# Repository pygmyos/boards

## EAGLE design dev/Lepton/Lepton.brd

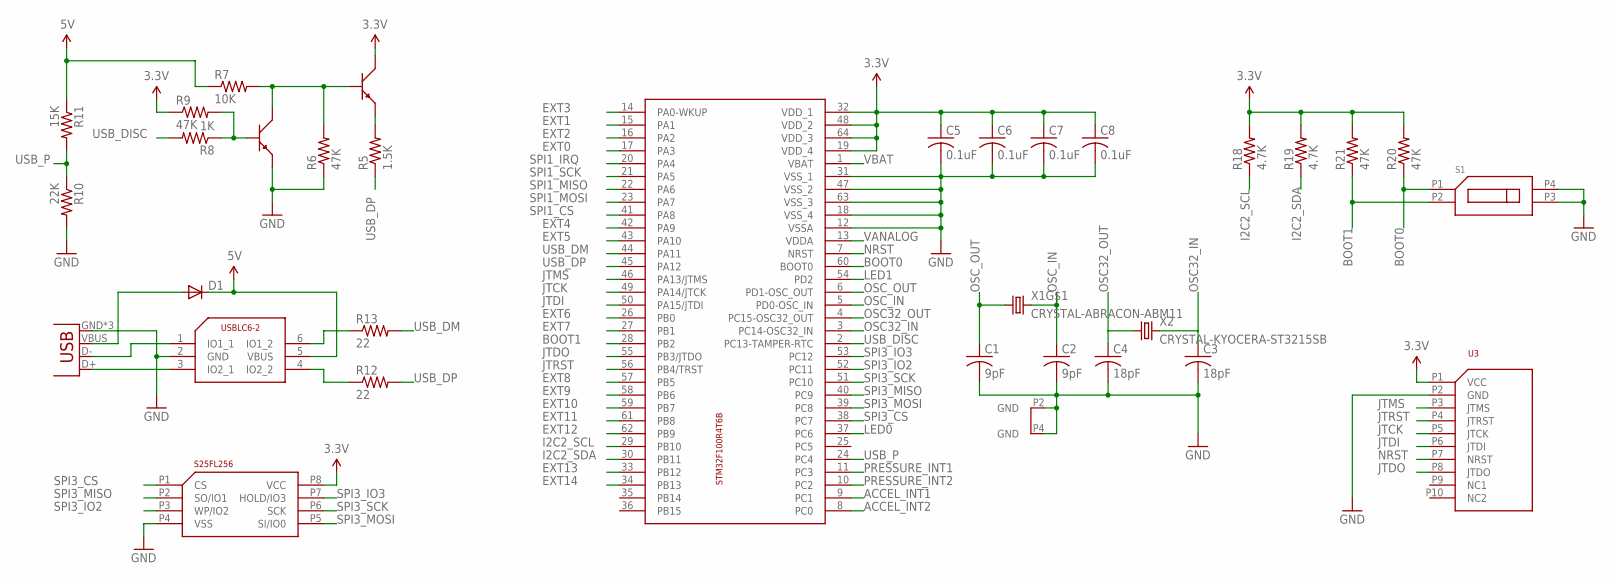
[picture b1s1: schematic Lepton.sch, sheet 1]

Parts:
C1, C2: 9pF; C0201
C3, C4: 18pF; C0201
C5, C6, C7, C8: 0.1uF; C0201
D1: DIODE-MINIMELF; MINIMELF
JP1: USB-MICROB
R5: 1.5K; R0402
R6: 47K; R0402
R7: 10K; R0201
R8: 1K; R0201
R9, R20, R21: 47K; R0201
R10: 22K; R0201
R11: 15K; R0201
R12, R13: 22; R0201
R18, R19: 4.7K; R0201
S1: SWITCH-DIP-GDH-02
U2: STM32F100R4T6B; S-PQFP64-G64
U3: STM32-JTAG-FFC; FCI-FFC-10P-51281-1494
U$1: SPANSION-S25FL256; SPANSION-WSON-8
U$2, U$3: BIPOLAR-PMBT6428; DUBLIB_SOT23
U$4: USBLC6-2; SOT23-6L
X1: CRYSTAL-ABRACON-ABM11; ABM11
X2: CRYSTAL-KYOCERA-ST3215SB

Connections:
3.3V: C5.1, C6.1, C7.1, C8.1, R9.1, R18.2, R19.2, R20.2, R21.2, U2.19 (VDD_4), U2.32 (VDD_1), U2.48 (VDD_2), U2.64 (VDD_3), U3.P1 (VCC), U$1.P8 (VCC), U$2.3; also elsewhere on the board
5V: D1.C, R7.1, R11.1, U$4.5 (VBUS); also elsewhere on the board
ACCEL_INT1: U2.9 (PC1)
ACCEL_INT2: U2.8 (PC0); also elsewhere on the board
BOOT0: R20.1, S1.P1 (SW0_0), U2.60 (BOOT0)
BOOT1: R21.1, S1.P2 (SW1_0), U2.28 (PB2)
EXT0: U2.17 (PA3); also elsewhere on the board
EXT1: U2.15 (PA1); also elsewhere on the board
EXT2: U2.16 (PA2); also elsewhere on the board
EXT3: U2.14 (PA0-WKUP); also elsewhere on the board
EXT4: U2.42 (PA9); also elsewhere on the board
EXT5: U2.43 (PA10); also elsewhere on the board
EXT6: U2.26 (PB0); also elsewhere on the board
EXT7: U2.27 (PB1); also elsewhere on the board
EXT8: U2.57 (PB5); also elsewhere on the board
EXT9: U2.58 (PB6); also elsewhere on the board
EXT10: U2.59 (PB7); also elsewhere on the board
EXT11: U2.61 (PB8); also elsewhere on the board
EXT12: U2.62 (PB9); also elsewhere on the board
EXT13: U2.33 (PB12); also elsewhere on the board
EXT14: U2.34 (PB13); also elsewhere on the board
GND: C1.2, C2.2, C3.2, C4.2, C5.2, C6.2, C7.2, C8.2, JP1.GND, JP1.MT1 (GND), JP1.MT2 (GND), R6.1, R10.2, S1.P3 (SW1_1), S1.P4 (SW0_1), U2.12 (VSSA), U2.18 (VSS_4), U2.31 (VSS_1), U2.47 (VSS_2), U2.63 (VSS_3), U3.P2 (GND), U$1.P4 (VSS), U$3.2, U$4.2 (GND), X1.P2 (GND), X1.P4 (GND); also elsewhere on the board
I2C2_SCL: R18.1, U2.29 (PB10); also elsewhere on the board
I2C2_SDA: R19.1, U2.30 (PB11); also elsewhere on the board
JTCK: U2.49 (PA14/JTCK), U3.P5 (JTCK)
JTDI: U2.50 (PA15/JTDI), U3.P6 (JTDI)
JTDO: U2.55 (PB3/JTDO), U3.P8 (JTDO)
JTMS: U2.46 (PA13/JTMS), U3.P3 (JTMS)
JTRST: U2.56 (PB4/TRST), U3.P4 (JTRST)
LED0: U2.37 (PC6); also elsewhere on the board
LED1: U2.54 (PD2); also elsewhere on the board
unnamed: JP1.D+, U$4.3 (IO2_1)
unnamed: JP1.D-, U$4.1 (IO1_1)
unnamed: D1.A, JP1.VBUS
unnamed: R13.1, U$4.6 (IO1_2)
unnamed: R5.2, U$2.2
unnamed: R6.2, R7.2, U$2.1, U$3.3
unnamed: R8.1, R9.2, U$3.1
unnamed: R12.1, U$4.4 (IO2_2)
NRST: U2.7 (NRST), U3.P7 (NRST)
OSC32_IN: C3.1, U2.3 (PC14-OSC32_IN), X2.P2 (2)
OSC32_OUT: C4.1, U2.4 (PC15-OSC32_OUT), X2.P1 (1)
OSC_IN: C2.1, U2.5 (PD0-OSC_IN), X1.P3 (2)
OSC_OUT: C1.1, U2.6 (PD1-OSC_OUT), X1.P1 (1)
PRESSURE_INT1: U2.11 (PC3); also elsewhere on the board
PRESSURE_INT2: U2.10 (PC2); also elsewhere on the board
SPI1_CS: U2.41 (PA8); also elsewhere on the board
SPI1_IRQ: U2.20 (PA4); also elsewhere on the board
SPI1_MISO: U2.22 (PA6); also elsewhere on the board
SPI1_MOSI: U2.23 (PA7); also elsewhere on the board
SPI1_SCK: U2.21 (PA5); also elsewhere on the board
SPI3_CS: U2.38 (PC7), U$1.P1 (CS)
SPI3_IO2: U2.52 (PC11), U$1.P3 (WP/IO2)
SPI3_IO3: U2.53 (PC12), U$1.P7 (HOLD/IO3)
SPI3_MISO: U2.40 (PC9), U$1.P2 (SO/IO1)
SPI3_MOSI: U2.39 (PC8), U$1.P5 (SI/IO0)
SPI3_SCK: U2.51 (PC10), U$1.P6 (SCK)
USB_DISC: R8.2, U2.2 (PC13-TAMPER-RTC); also elsewhere on the board
USB_DM: R13.2, U2.44 (PA11); also elsewhere on the board
USB_DP: R5.1, R12.2, U2.45 (PA12); also elsewhere on the board
USB_P: R10.1, R11.2, U2.24 (PC4)
VANALOG: U2.13 (VDDA); also elsewhere on the board
VBAT: U2.1 (VBAT); also elsewhere on the board

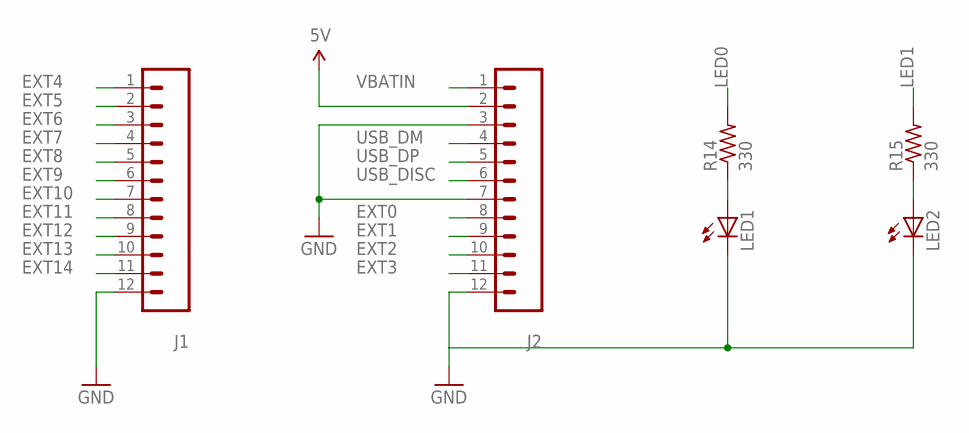
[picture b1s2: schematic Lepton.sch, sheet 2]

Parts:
J1, J2: M12; 1X12
LED1, LED2: LED0603; LED-0603
R14, R15: 330; R0201

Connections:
5V: J2.2; also elsewhere on the board
EXT0: J2.8; also elsewhere on the board
EXT1: J2.9; also elsewhere on the board
EXT2: J2.10; also elsewhere on the board
EXT3: J2.11; also elsewhere on the board
EXT4: J1.1; also elsewhere on the board
EXT5: J1.2; also elsewhere on the board
EXT6: J1.3; also elsewhere on the board
EXT7: J1.4; also elsewhere on the board
EXT8: J1.5; also elsewhere on the board
EXT9: J1.6; also elsewhere on the board
EXT10: J1.7; also elsewhere on the board
EXT11: J1.8; also elsewhere on the board
EXT12: J1.9; also elsewhere on the board
EXT13: J1.10; also elsewhere on the board
EXT14: J1.11; also elsewhere on the board
GND: J1.12, J2.3, J2.7, J2.12, LED1.C, LED2.C; also elsewhere on the board
LED0: R14.2; also elsewhere on the board
LED1: R15.2; also elsewhere on the board
unnamed: LED1.A, R14.1
unnamed: LED2.A, R15.1
USB_DISC: J2.6; also elsewhere on the board
USB_DM: J2.4; also elsewhere on the board
USB_DP: J2.5; also elsewhere on the board
VBATIN: J2.1; also elsewhere on the board

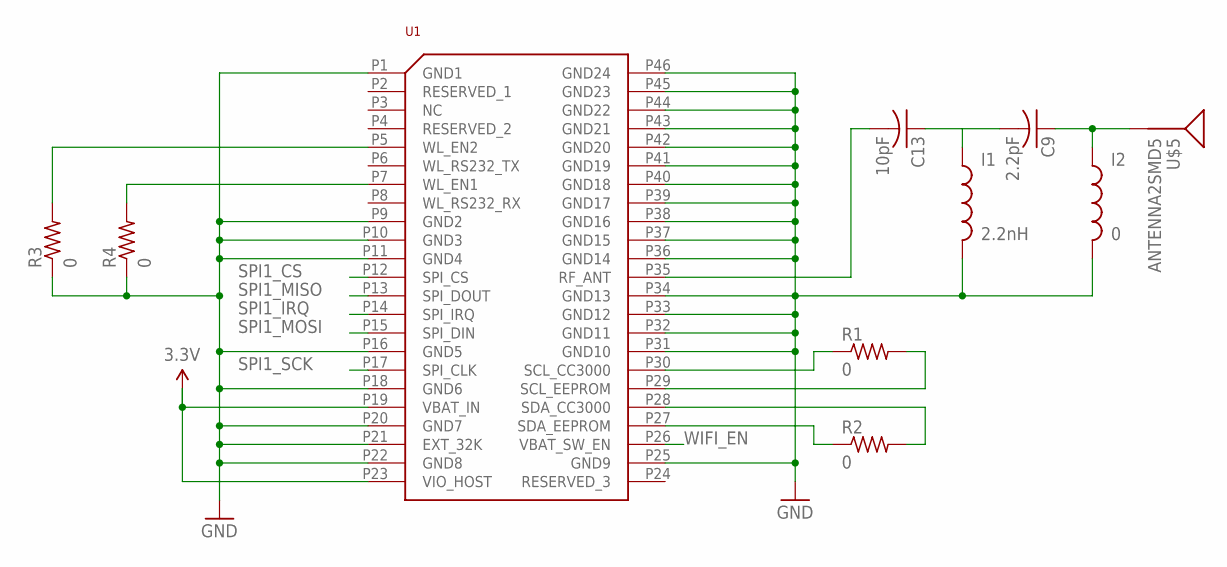
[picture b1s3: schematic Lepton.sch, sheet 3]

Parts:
C9: 2.2pF; C0201
C13: 10pF; C0201
I1: 2.2nH; C0402
I2: 0; C0402
R1, R2, R3, R4: 0; R0201
U1: CC3000
U$5: ANTENNA2SMD5; ANTENNA-CHIP5

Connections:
3.3V: U1.P19 (VBAT_IN), U1.P23 (VIO_HOST); also elsewhere on the board
ANT: C13.2, U1.P35 (RF_ANT)
GND: I1.2, I2.2, R3.1, R4.1, U1.P1 (GND1), U1.P9 (GND2), U1.P10 (GND3), U1.P11 (GND4), U1.P16 (GND5), U1.P18 (GND6), U1.P20 (GND7), U1.P21 (EXT_32K), U1.P22 (GND8), U1.P25 (GND9), U1.P31 (GND10), U1.P32 (GND11), U1.P33 (GND12), U1.P34 (GND13), U1.P36 (GND14), U1.P37 (GND15), U1.P38 (GND16), U1.P39 (GND17), U1.P40 (GND18), U1.P41 (GND19), U1.P42 (GND20), U1.P43 (GND21), U1.P44 (GND22), U1.P45 (GND23), U1.P46 (GND24); also elsewhere on the board
unnamed: C9.2, C13.1, I1.1
unnamed: R3.2, U1.P5 (WL_EN2)
unnamed: R4.2, U1.P7 (WL_EN1)
unnamed: C9.1, I2.1, U$5.FEED
unnamed: R1.1, U1.P30 (SCL_CC3000)
unnamed: R1.2, U1.P29 (SCL_EEPROM)
unnamed: R2.2, U1.P28 (SDA_CC3000)
unnamed: R2.1, U1.P27 (SDA_EEPROM)
SPI1_CS: U1.P12 (SPI_CS); also elsewhere on the board
SPI1_IRQ: U1.P14 (SPI_IRQ); also elsewhere on the board
SPI1_MISO: U1.P13 (SPI_DOUT); also elsewhere on the board
SPI1_MOSI: U1.P15 (SPI_DIN); also elsewhere on the board
SPI1_SCK: U1.P17 (SPI_CLK); also elsewhere on the board
WIFI_EN: U1.P26 (VBAT_SW_EN)

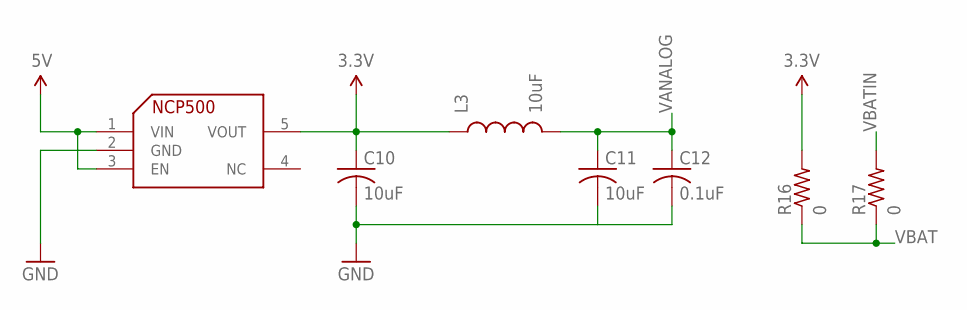
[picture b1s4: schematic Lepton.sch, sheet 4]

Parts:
C10, C11: 10uF; C0603
C12: 0.1uF; C0201
L3: 10uF; 0603
R16, R17: 0; R0402
U$7: NCP500; SOT23-5L

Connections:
3.3V: C10.1, L3.1, R16.2, U$7.5 (VOUT); also elsewhere on the board
5V: U$7.1 (VIN), U$7.3 (EN); also elsewhere on the board
GND: C10.2, C11.2, C12.2, U$7.2 (GND); also elsewhere on the board
VANALOG: C11.1, C12.1, L3.2; also elsewhere on the board
VBAT: R16.1, R17.1; also elsewhere on the board
VBATIN: R17.2; also elsewhere on the board

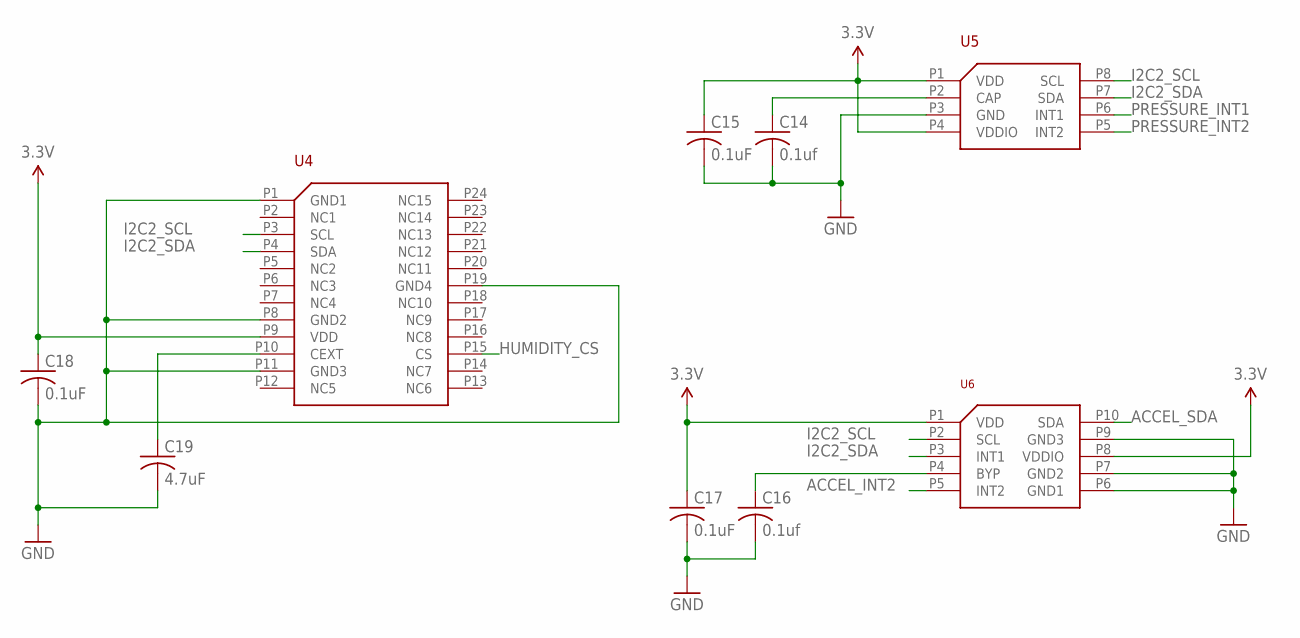
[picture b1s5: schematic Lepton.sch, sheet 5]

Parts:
C14, C16: 0.1uf; C0201
C15, C17, C18: 0.1uF; C0201
C19: 4.7uF; C0402
U4: SILICONLABS-HUMIDITY-SI7005; SILICONLABS-TQFN-24
U5: FREESCALE-PRESSURE-MPL3115A2; UQFN-8L
U6: MMA8653FC; DFN-2X2-10

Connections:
3.3V: C15.1, C17.1, C18.1, U4.P9 (VDD), U5.P1 (VDD), U5.P4 (VDDIO), U6.P1 (VDD), U6.P8 (VDDIO); also elsewhere on the board
ACCEL_INT2: U6.P5 (INT2); also elsewhere on the board
ACCEL_SDA: U6.P10 (SDA)
GND: C14.2, C15.2, C16.2, C17.2, C18.2, C19.2, U4.P1 (GND1), U4.P8 (GND2), U4.P11 (GND3), U4.P19 (GND4), U5.P3 (GND), U6.P6 (GND1), U6.P7 (GND2), U6.P9 (GND3); also elsewhere on the board
HUMIDITY_CS: U4.P15 (CS)
I2C2_SCL: U4.P3 (SCL), U5.P8 (SCL), U6.P2 (SCL); also elsewhere on the board
I2C2_SDA: U4.P4 (SDA), U5.P7 (SDA), U6.P3 (INT1); also elsewhere on the board
unnamed: C16.1, U6.P4 (BYP)
unnamed: C19.1, U4.P10 (CEXT)
unnamed: C14.1, U5.P2 (CAP)
PRESSURE_INT1: U5.P6 (INT1); also elsewhere on the board
PRESSURE_INT2: U5.P5 (INT2); also elsewhere on the board

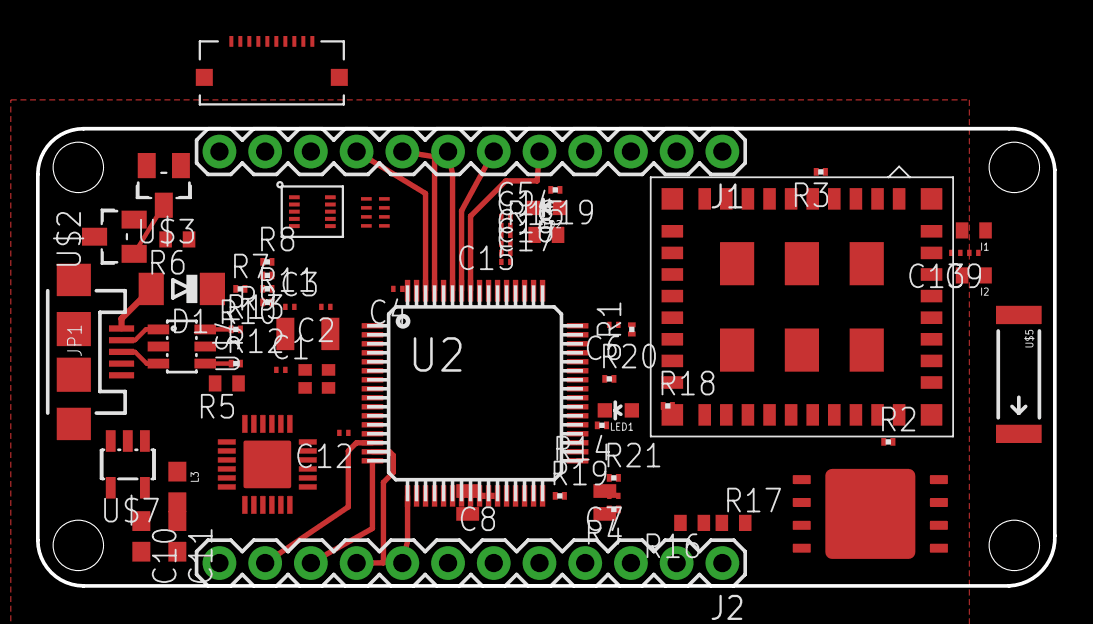
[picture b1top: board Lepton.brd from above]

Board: 4 copper layers, 56.5 x 25.4 mm, 64 parts (0 on the bottom side), 77 nets.

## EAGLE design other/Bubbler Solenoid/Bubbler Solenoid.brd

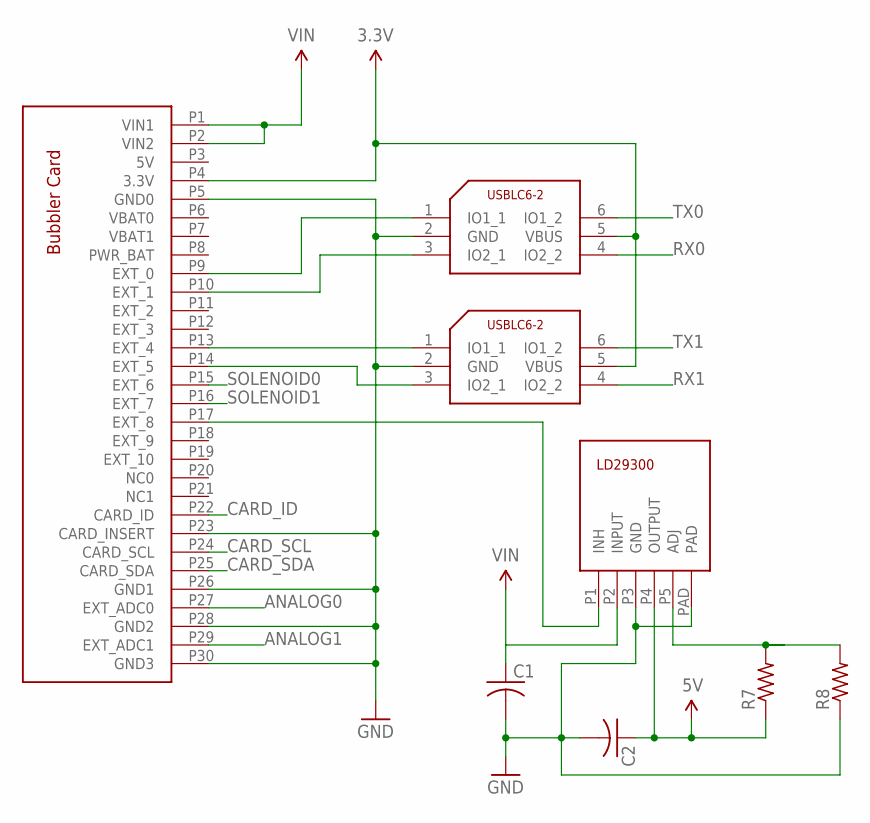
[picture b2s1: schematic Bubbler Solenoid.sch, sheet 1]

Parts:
C1, C2: C-USC0805; C0805
R7, R8: R-US_R0402; R0402
U1: BUBBLER_CARD; CONNECTOR-JAE-TX24-30M
U10, U11: USBLC6-2; SOT23-6L
U$3: LD29300P2MTR; P2PAK/A

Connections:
3.3V: U1.P4 (3.3V), U10.5 (VBUS), U11.5 (VBUS); also elsewhere on the board
5V: C2.1, R7.1, U$3.P4 (OUTPUT); also elsewhere on the board
ANALOG0: U1.P27 (EXT_ADC0); also elsewhere on the board
ANALOG1: U1.P29 (EXT_ADC1); also elsewhere on the board
CARD_ID: U1.P22 (CARD_ID); also elsewhere on the board
CARD_SCL: U1.P24 (CARD_SCL); also elsewhere on the board
CARD_SDA: U1.P25 (CARD_SDA); also elsewhere on the board
GND: C1.2, C2.2, R8.1, U1.P5 (GND0), U1.P23 (CARD_INSERT), U1.P26 (GND1), U1.P28 (GND2), U1.P30 (GND3), U10.2 (GND), U11.2 (GND), U$3.P3 (GND), U$3.PAD; also elsewhere on the board
unnamed: U1.P9 (EXT_0), U10.1 (IO1_1)
unnamed: U1.P10 (EXT_1), U10.3 (IO2_1)
unnamed: U1.P13 (EXT_4), U11.1 (IO1_1)
unnamed: U1.P14 (EXT_5), U11.3 (IO2_1)
unnamed: U1.P17 (EXT_8), U$3.P1 (INH)
unnamed: R7.2, R8.2, U$3.P5 (ADJ)
RX0: U10.4 (IO2_2); also elsewhere on the board
RX1: U11.4 (IO2_2); also elsewhere on the board
SOLENOID0: U1.P15 (EXT_6); also elsewhere on the board
SOLENOID1: U1.P16 (EXT_7); also elsewhere on the board
TX0: U10.6 (IO1_2); also elsewhere on the board
TX1: U11.6 (IO1_2); also elsewhere on the board
VIN: C1.1, U1.P1 (VIN1), U1.P2 (VIN2), U$3.P2 (INPUT)

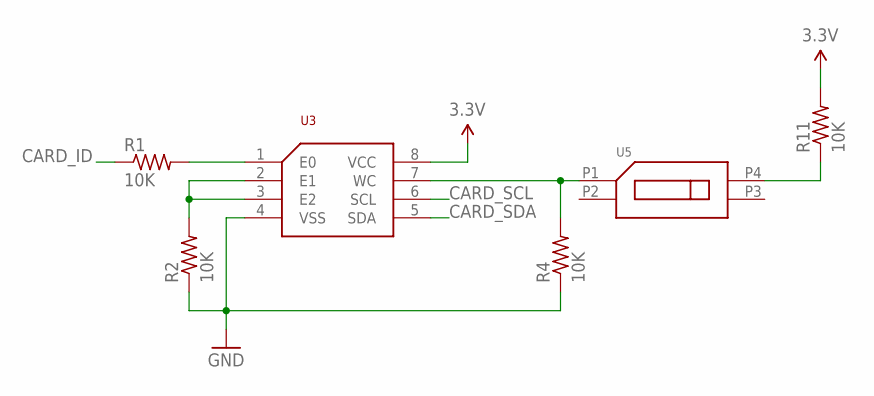
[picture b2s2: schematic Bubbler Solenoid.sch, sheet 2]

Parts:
R1, R2, R4, R11: 10K; R0402
U3: EEPROM-ST-M24C64; TSSOP8
U5: SWITCH-DIP-GDH-02

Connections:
3.3V: R11.2, U3.8 (VCC); also elsewhere on the board
CARD_ID: R1.1; also elsewhere on the board
CARD_SCL: U3.6 (SCL); also elsewhere on the board
CARD_SDA: U3.5 (SDA); also elsewhere on the board
GND: R2.1, R4.1, U3.4 (VSS); also elsewhere on the board
unnamed: R2.2, U3.2 (E1), U3.3 (E2)
unnamed: R1.2, U3.1 (E0)
unnamed: R11.1, U5.P4 (SW0_1)
unnamed: R4.2, U3.7 (WC), U5.P1 (SW0_0)

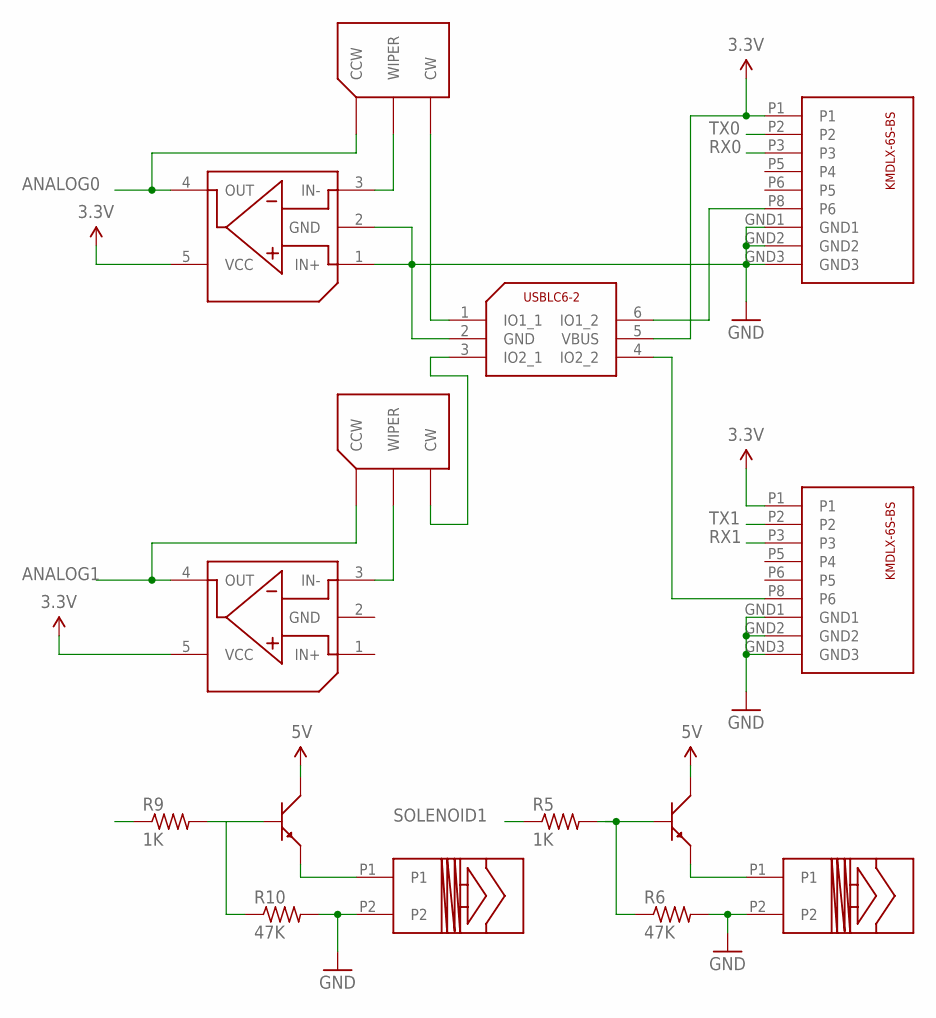
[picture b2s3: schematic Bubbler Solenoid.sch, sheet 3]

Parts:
R5, R9: 1K; R0402
R6, R10: 47K; R0402
U2, U4: OPAMP-ST-LMV321ILT; SOT23-5L
U6, U8: BIPOLAR-PMBT6428; DUBLIB_SOT23
U9: USBLC6-2; SOT23-6L
U12, U13: BOURNES-TC73; TC73X
U$1, U$4: KMDLX-6S-BS
U$5, U$7: PARKER-XVALVE-8MM

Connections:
3.3V: U2.5 (VCC), U4.5 (VCC), U9.5 (VBUS), U$1.P1, U$4.P1; also elsewhere on the board
5V: U6.3, U8.3; also elsewhere on the board
ANALOG0: U4.4 (OUT), U13.P$1 (CCW); also elsewhere on the board
ANALOG1: U2.4 (OUT), U12.P$1 (CCW); also elsewhere on the board
GND: R6.2, R10.2, U4.1 (IN+), U4.2 (GND), U9.2 (GND), U$1.GND1, U$1.GND2, U$1.GND3, U$4.GND1, U$4.GND2, U$4.GND3, U$5.P2, U$7.P2; also elsewhere on the board
unnamed: U6.2, U$5.P1
unnamed: R5.2, R6.1, U6.1
unnamed: U8.2, U$7.P1
unnamed: U9.1 (IO1_1), U13.P$3 (CW)
unnamed: R9.2, R10.1, U8.1
unnamed: U2.3 (IN-), U12.P$2 (WIPER)
unnamed: U9.3 (IO2_1), U12.P$3 (CW)
unnamed: U9.6 (IO1_2), U$1.P8 (P6)
unnamed: U9.4 (IO2_2), U$4.P8 (P6)
unnamed: U4.3 (IN-), U13.P$2 (WIPER)
RX0: U$1.P3; also elsewhere on the board
RX1: U$4.P3; also elsewhere on the board
SOLENOID0: R9.1; also elsewhere on the board
SOLENOID1: R5.1; also elsewhere on the board
TX0: U$1.P2; also elsewhere on the board
TX1: U$4.P2; also elsewhere on the board

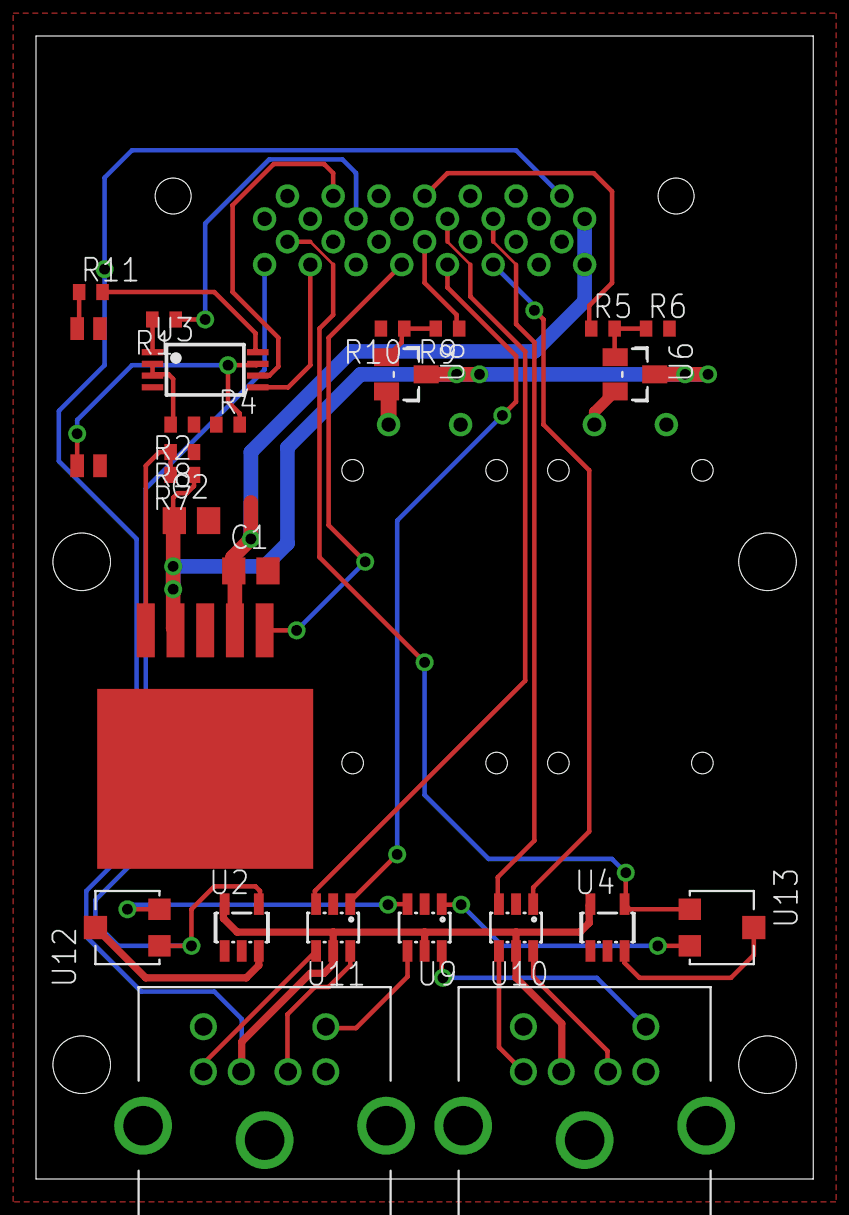
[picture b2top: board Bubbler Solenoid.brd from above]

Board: 2 copper layers, 43.2 x 63.5 mm, 29 parts (0 on the bottom side), 35 nets.

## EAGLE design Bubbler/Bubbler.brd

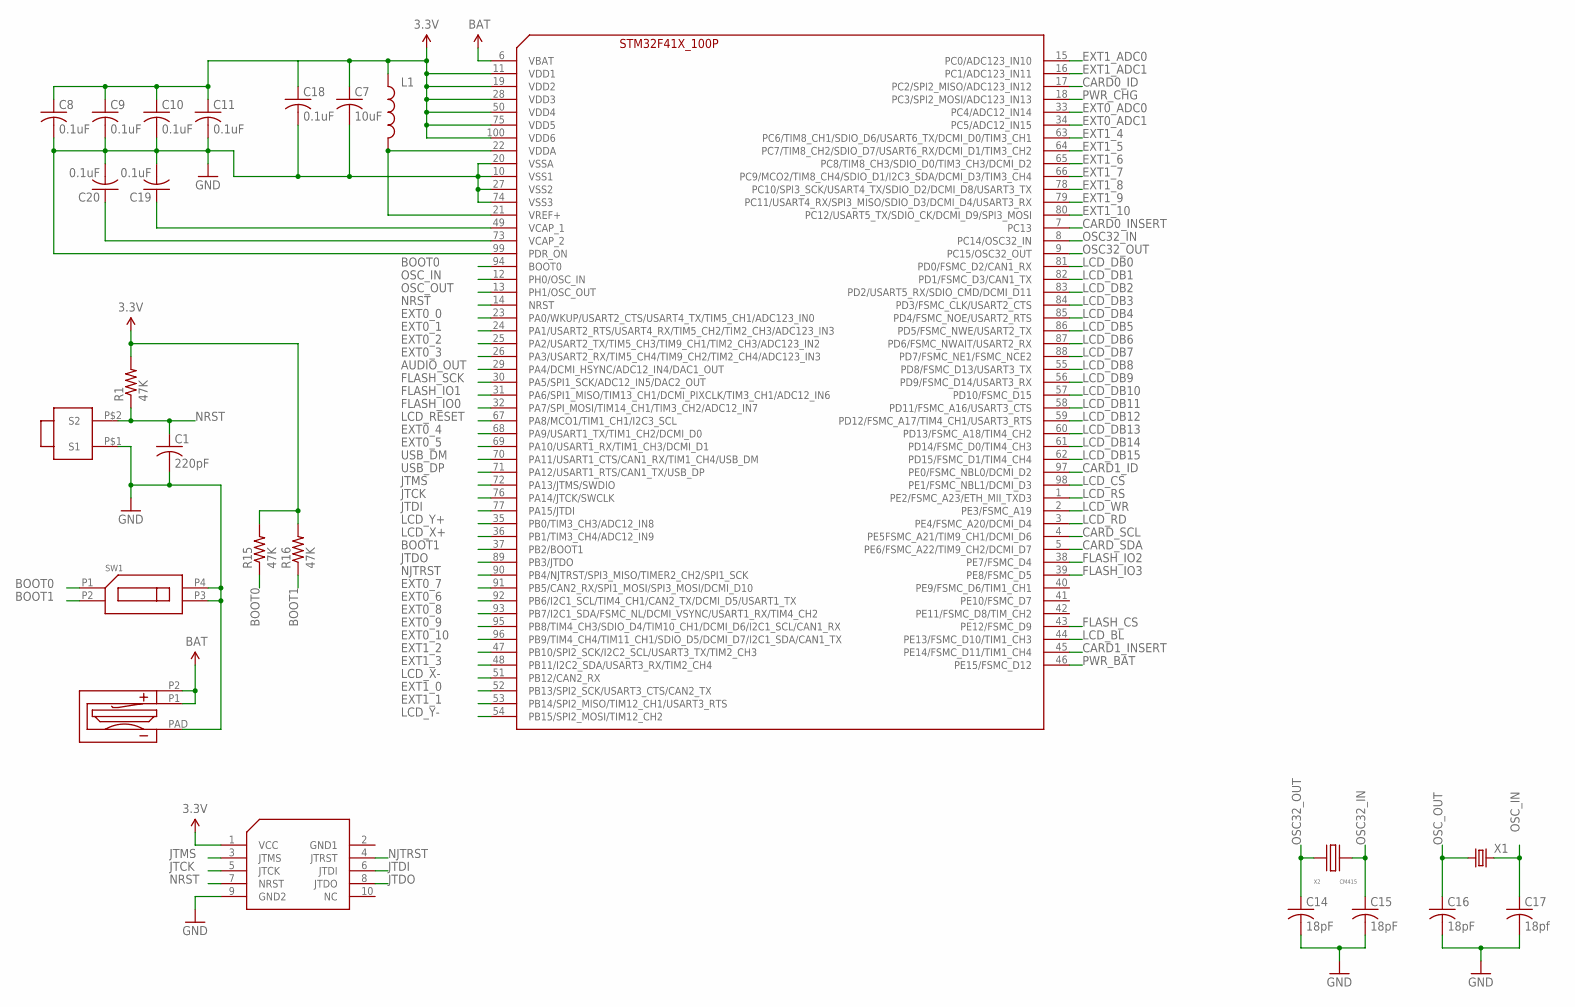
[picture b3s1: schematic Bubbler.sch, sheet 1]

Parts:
B1: BATTERY-LINX-HLD-001
C1: 220pF; C0402
C7: 10uF; C0805
C8, C9, C10, C11, C18, C19, C20: 0.1uF; C0402
C14, C15, C16: 18pF; C0402
C17: 18pf; C0402
L1: INDUCTOR0603; 0603
R1, R15, R16: 47K; R0402
SW1: SWITCH-DIP-GDH-02
SW2: ITT-SWITCH-KSS-G; ITT-KSS-G
U1: STM32F41X-100P; TQFP100
U$1: STM32-JTAG-10P
X1: CRYSTAL5X3; CRYSTAL-SMD-5X3
X2: CM415

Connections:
3.3V: C7.1, C8.1, C9.1, C10.1, C11.1, C18.1, L1.1, R1.2, R15.2, R16.2, U1.11 (VDD1), U1.19 (VDD2), U1.28 (VDD3), U1.50 (VDD4), U1.75 (VDD5), U1.100 (VDD6), U$1.1 (VCC); also elsewhere on the board
AUDIO_OUT: U1.29 (PA4/DCMI_HSYNC/ADC12_IN4/DAC1_OUT); also elsewhere on the board
BAT: B1.P1 (BAT1), B1.P2 (BAT2), U1.6 (VBAT)
BOOT0: R15.1, SW1.P1 (SW0_0), U1.94 (BOOT0)
BOOT1: R16.1, SW1.P2 (SW1_0), U1.37 (PB2/BOOT1)
CARD0_ID: U1.17 (PC2/SPI2_MISO/ADC123_IN12); also elsewhere on the board
CARD0_INSERT: U1.7 (PC13); also elsewhere on the board
CARD1_ID: U1.97 (PE0/FSMC_NBL0/DCMI_D2); also elsewhere on the board
CARD1_INSERT: U1.45 (PE14/FSMC_D11/TIM1_CH4); also elsewhere on the board
CARD_SCL: U1.4 (PE5FSMC_A21/TIM9_CH1/DCMI_D6); also elsewhere on the board
CARD_SDA: U1.5 (PE6/FSMC_A22/TIM9_CH2/DCMI_D7); also elsewhere on the board
EXT0_0: U1.23 (PA0/WKUP/USART2_CTS/USART4_TX/TIM5_CH1/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); also elsewhere on the board
EXT0_1: U1.24 (PA1/USART2_RTS/USART4_RX/TIM5_CH2/TIM2_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); also elsewhere on the board
EXT0_2: U1.25 (PA2/USART2_TX/TIM5_CH3/TIM9_CH1/TIM2_CH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); also elsewhere on the board
EXT0_3: U1.26 (PA3/USART2_RX/TIM5_CH4/TIM9_CH2/TIM2_CH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); also elsewhere on the board
EXT0_4: U1.68 (PA9/USART1_TX/TIM1_CH2/DCMI_D0); also elsewhere on the board
EXT0_5: U1.69 (PA10/USART1_RX/TIM1_CH3/DCMI_D1); also elsewhere on the board
EXT0_6: U1.92 (PB6/I2C1_SCL/TIM4_CH1/CAN2_TX/DCMI_D5/U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); also elsewhere on the board
EXT0_7: U1.91 (PB5/CAN2_RX/SPI1_MOSI/SPI3_MOSI/DCMI_D10); also elsewhere on the board
EXT0_8: U1.93 (PB7/I2C1_SDA/FSMC_NL/DCMI_VSYNC/USART1_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); also elsewhere on the board
EXT0_9: U1.95 (PB8/TIM4_CH3/SDIO_D4/TIM10_CH1/DCMI_D6/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); also elsewhere on the board
EXT0_10: U1.96 (PB9/TIM4_CH4/TIM11_CH1/SDIO_D5/DCMI_D7/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); also elsewhere on the board
EXT0_ADC0: U1.33 (PC4/ADC12_IN14); also elsewhere on the board
EXT0_ADC1: U1.34 (PC5/ADC12_IN15); also elsewhere on the board
EXT1_0: U1.52 (PB13/SPI2_SCK/USART3_CTS/CAN2_TX); also elsewhere on the board
EXT1_1: U1.53 (PB14/SPI2_MISO/TIM12_CH1/USART3_RTS); also elsewhere on the board
EXT1_2: U1.47 (PB10/SPI2_SCK/I2C2_SCL/USART3_TX/TIM2_C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); also elsewhere on the board
EXT1_3: U1.48 (PB11/I2C2_SDA/USART3_RX/TIM2_CH4); also elsewhere on the board
EXT1_4: U1.63 (PC6/TIM8_CH1/SDIO_D6/USART6_TX/DCMI_D0/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); also elsewhere on the board
EXT1_5: U1.64 (PC7/TIM8_CH2/SDIO_D7/USART6_RX/DCMI_D1/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); also elsewhere on the board
EXT1_6: U1.65 (PC8/TIM8_CH3/SDIO_D0/TIM3_CH3/DCMI_D2); also elsewhere on the board
EXT1_7: U1.66 (PC9/MCO2/TIM8_CH4/SDIO_D1/I2C3_SDA/DCMI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); also elsewhere on the board
EXT1_8: U1.78 (PC10/SPI3_SCK/USART4_TX/SDIO_D2/DCMI_D8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); also elsewhere on the board
EXT1_9: U1.79 (PC11/USART4_RX/SPI3_MISO/SDIO_D3/DCMI_D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); also elsewhere on the board
EXT1_10: U1.80 (PC12/USART5_TX/SDIO_CK/DCMI_D9/SPI3_MOSI); also elsewhere on the board
EXT1_ADC0: U1.15 (PC0/ADC123_IN10); also elsewhere on the board
EXT1_ADC1: U1.16 (PC1/ADC123_IN11); also elsewhere on the board
FLASH_CS: U1.43 (PE12/FSMC_D9); also elsewhere on the board
FLASH_IO0: U1.32 (PA7/SPI_MOSI/TIM14_CH1/TIM3_CH2/ADC12_I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); also elsewhere on the board
FLASH_IO1: U1.31 (PA6/SPI1_MISO/TIM13_CH1/DCMI_PIXCLK/TIM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); also elsewhere on the board
FLASH_IO2: U1.38 (PE7/FSMC_D4); also elsewhere on the board
FLASH_IO3: U1.39 (PE8/FSMC_D5); also elsewhere on the board
FLASH_SCK: U1.30 (PA5/SPI1_SCK/ADC12_IN5/DAC2_OUT); also elsewhere on the board
GND: B1.PAD (GND), C1.2, C7.2, C8.2, C9.2, C10.2, C11.2, C14.2, C15.2, C16.2, C17.2, C18.2, C19.2, C20.2, SW1.P3 (SW1_1), SW1.P4 (SW0_1), SW2.P$1 (S1), U1.10 (VSS1), U1.20 (VSSA), U1.27 (VSS2), U1.74 (VSS3), U1.99 (PDR_ON), U$1.9 (GND2); also elsewhere on the board
JTCK: U1.76 (PA14/JTCK/SWCLK), U$1.5 (JTCK)
JTDI: U1.77 (PA15/JTDI), U$1.6 (JTDI)
JTDO: U1.89 (PB3/JTDO), U$1.8 (JTDO)
JTMS: U1.72 (PA13/JTMS/SWDIO), U$1.3 (JTMS)
LCD_BL: U1.44 (PE13/FSMC_D10/TIM1_CH3); also elsewhere on the board
LCD_CS: U1.98 (PE1/FSMC_NBL1/DCMI_D3); also elsewhere on the board
LCD_DB0: U1.81 (PD0/FSMC_D2/CAN1_RX); also elsewhere on the board
LCD_DB1: U1.82 (PD1/FSMC_D3/CAN1_TX); also elsewhere on the board
LCD_DB2: U1.83 (PD2/USART5_RX/SDIO_CMD/DCMI_D11); also elsewhere on the board
LCD_DB3: U1.84 (PD3/FSMC_CLK/USART2_CTS); also elsewhere on the board
LCD_DB4: U1.85 (PD4/FSMC_NOE/USART2_RTS); also elsewhere on the board
LCD_DB5: U1.86 (PD5/FSMC_NWE/USART2_TX); also elsewhere on the board
LCD_DB6: U1.87 (PD6/FSMC_NWAIT/USART2_RX); also elsewhere on the board
LCD_DB7: U1.88 (PD7/FSMC_NE1/FSMC_NCE2); also elsewhere on the board
LCD_DB8: U1.55 (PD8/FSMC_D13/USART3_TX); also elsewhere on the board
LCD_DB9: U1.56 (PD9/FSMC_D14/USART3_RX); also elsewhere on the board
LCD_DB10: U1.57 (PD10/FSMC_D15); also elsewhere on the board
LCD_DB11: U1.58 (PD11/FSMC_A16/USART3_CTS); also elsewhere on the board
LCD_DB12: U1.59 (PD12/FSMC_A17/TIM4_CH1/USART3_RTS); also elsewhere on the board
LCD_DB13: U1.60 (PD13/FSMC_A18/TIM4_CH2); also elsewhere on the board
LCD_DB14: U1.61 (PD14/FSMC_D0/TIM4_CH3); also elsewhere on the board
LCD_DB15: U1.62 (PD15/FSMC_D1/TIM4_CH4); also elsewhere on the board
LCD_RD: U1.3 (PE4/FSMC_A20/DCMI_D4); also elsewhere on the board
LCD_RESET: U1.67 (PA8/MCO1/TIM1_CH1/I2C3_SCL); also elsewhere on the board
LCD_RS: U1.1 (PE2/FSMC_A23/ETH_MII_TXD3); also elsewhere on the board
LCD_WR: U1.2 (PE3/FSMC_A19); also elsewhere on the board
LCD_X+: U1.36 (PB1/TIM3_CH4/ADC12_IN9); also elsewhere on the board
LCD_X-: U1.51 (PB12/CAN2_RX); also elsewhere on the board
LCD_Y+: U1.35 (PB0/TIM3_CH3/ADC12_IN8); also elsewhere on the board
LCD_Y-: U1.54 (PB15/SPI2_MOSI/TIM12_CH2); also elsewhere on the board
unnamed: L1.2, U1.21 (VREF+), U1.22 (VDDA)
unnamed: C19.1, U1.49 (VCAP_1)
unnamed: C20.1, U1.73 (VCAP_2)
NJTRST: U1.90 (PB4/NJTRST/SPI3_MISO/TIMER2_CH2/SPI1_SCK), U$1.4 (JTRST)
NRST: C1.1, R1.1, SW2.P$2 (S2), U1.14 (NRST), U$1.7 (NRST)
OSC32_IN: C15.1, U1.8 (PC14/OSC32_IN), X2.P$2 (XOUT)
OSC32_OUT: C14.1, U1.9 (PC15/OSC32_OUT), X2.P$1 (XIN)
OSC_IN: C17.1, U1.12 (PH0/OSC_IN), X1.3 (2)
OSC_OUT: C16.1, U1.13 (PH1/OSC_OUT), X1.1
PWR_BAT: U1.46 (PE15/FSMC_D12); also elsewhere on the board
PWR_CHG: U1.18 (PC3/SPI2_MOSI/ADC123_IN13); also elsewhere on the board
USB_DM: U1.70 (PA11/USART1_CTS/CAN1_RX/TIM1_CH4/USB_DM); also elsewhere on the board
USB_DP: U1.71 (PA12/USART1_RTS/CAN1_TX/USB_DP); also elsewhere on the board

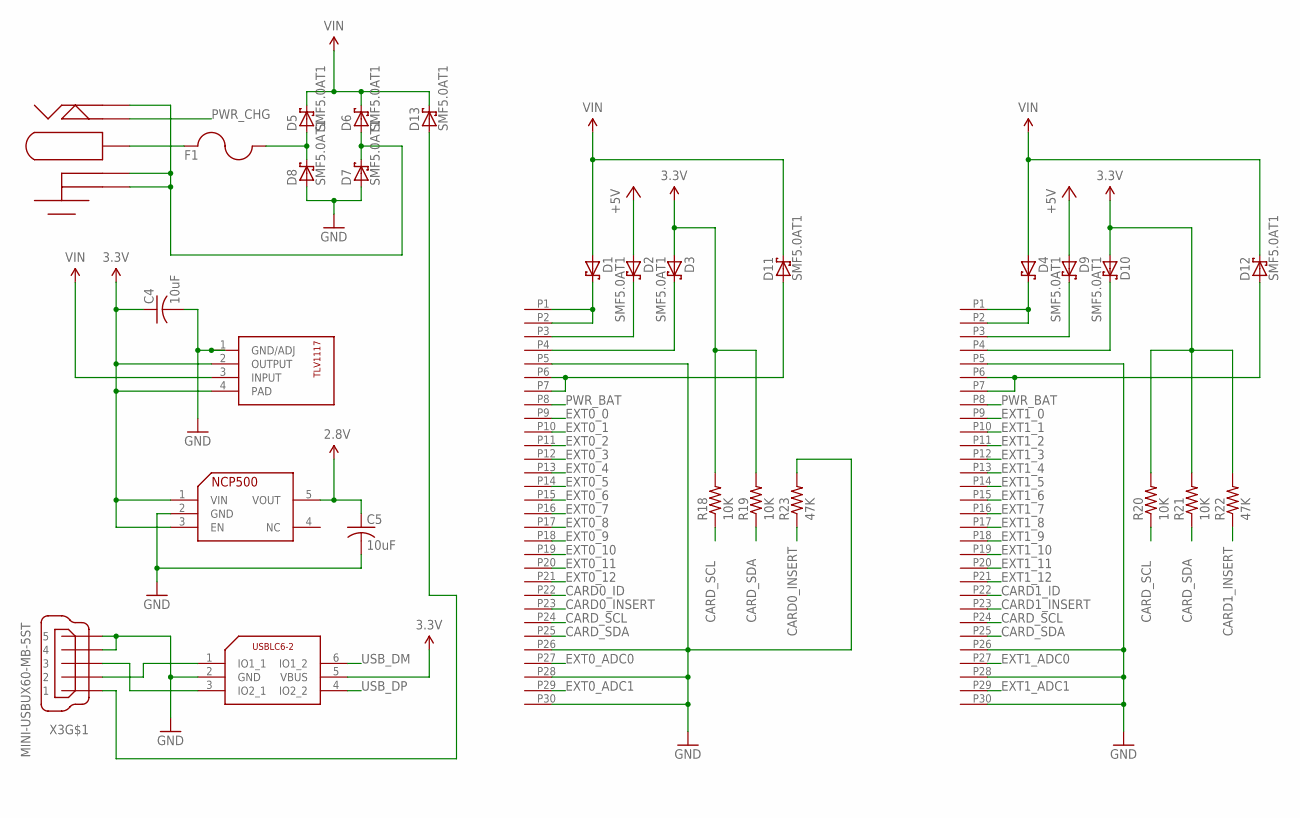
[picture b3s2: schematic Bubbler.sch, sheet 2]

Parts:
C4, C5: 10uF; C1206
CARD0, CARD1: CONNECTOR-JAE-TX24-30F; CONNECTOR-JAE-TX24-30
D1, D4: SCHOTTKY-DIODESMD; SMB
D2, D3, D5, D6, D7, D8, D9, D10, D11, D12, D13: SMF5.0AT1; SOD123FL
F1: BOURNES-PTC-MF-SMXXXMF-SM030; MF-SM030
R18, R19, R20, R21: 10K; R0402
R22, R23: 47K; R0402
U5: USBLC6-2; SOT23-6L
U6: TLV1117; SOT223
U$2: DCJACK-CUI-PJ051AH; DCJACK_CUI_PJ012B
U$7: NCP500; SOT23-5L
X3: MINI-USBUX60-MB-5ST; DUBLIB_UX60-MB-5ST

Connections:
2.8V: C5.1, U$7.5 (VOUT); also elsewhere on the board
3.3V: C4.1, D3.A, D10.A, R18.2, R19.2, R20.2, R21.2, R22.2, U5.5 (VBUS), U6.2 (OUTPUT), U6.4 (PAD), U$7.1 (VIN), U$7.3 (EN); also elsewhere on the board
+5V: D2.A, D9.A
CARD0_ID: CARD0.P22; also elsewhere on the board
CARD0_INSERT: CARD0.P23, R23.1; also elsewhere on the board
CARD1_ID: CARD1.P22; also elsewhere on the board
CARD1_INSERT: CARD1.P23, R22.1; also elsewhere on the board
CARD_SCL: CARD0.P24, CARD1.P24, R18.1, R20.1; also elsewhere on the board
CARD_SDA: CARD0.P25, CARD1.P25, R19.1, R21.1; also elsewhere on the board
EXT0_0: CARD0.P9; also elsewhere on the board
EXT0_1: CARD0.P10; also elsewhere on the board
EXT0_2: CARD0.P11; also elsewhere on the board
EXT0_3: CARD0.P12; also elsewhere on the board
EXT0_4: CARD0.P13; also elsewhere on the board
EXT0_5: CARD0.P14; also elsewhere on the board
EXT0_6: CARD0.P15; also elsewhere on the board
EXT0_7: CARD0.P16; also elsewhere on the board
EXT0_8: CARD0.P17; also elsewhere on the board
EXT0_9: CARD0.P18; also elsewhere on the board
EXT0_10: CARD0.P19; also elsewhere on the board
EXT0_11: CARD0.P20
EXT0_12: CARD0.P21
EXT0_ADC0: CARD0.P27; also elsewhere on the board
EXT0_ADC1: CARD0.P29; also elsewhere on the board
EXT1_0: CARD1.P9; also elsewhere on the board
EXT1_1: CARD1.P10; also elsewhere on the board
EXT1_2: CARD1.P11; also elsewhere on the board
EXT1_3: CARD1.P12; also elsewhere on the board
EXT1_4: CARD1.P13; also elsewhere on the board
EXT1_5: CARD1.P14; also elsewhere on the board
EXT1_6: CARD1.P15; also elsewhere on the board
EXT1_7: CARD1.P16; also elsewhere on the board
EXT1_8: CARD1.P17; also elsewhere on the board
EXT1_9: CARD1.P18; also elsewhere on the board
EXT1_10: CARD1.P19; also elsewhere on the board
EXT1_11: CARD1.P20
EXT1_12: CARD1.P21
EXT1_ADC0: CARD1.P27; also elsewhere on the board
EXT1_ADC1: CARD1.P29; also elsewhere on the board
GND: C4.2, C5.2, CARD0.P5, CARD0.P26, CARD0.P28, CARD0.P30, CARD1.P5, CARD1.P26, CARD1.P28, CARD1.P30, D7.A, D8.A, R23.2, U5.2 (GND), U6.1 (GND/ADJ), U$7.2 (GND), X3.4, X3.5, X3.M1 (GND), X3.M2 (GND), X3.M3 (GND), X3.M4 (GND); also elsewhere on the board
unnamed: CARD1.P4, D10.C
unnamed: D6.A, D7.C, U$2.GND1, U$2.GND2, U$2.P2
unnamed: F1.P$1, U$2.P1
unnamed: U5.1 (IO1_1), X3.2
unnamed: U5.3 (IO2_1), X3.3
unnamed: D5.A, D8.C, F1.P$2
unnamed: CARD0.P4, D3.C
unnamed: CARD0.P1, CARD0.P2, D1.C
unnamed: CARD1.P1, CARD1.P2, D4.C
unnamed: CARD0.P3, D2.C
unnamed: CARD0.P6, CARD0.P7, D11.A
unnamed: CARD1.P3, D9.C
unnamed: D13.A, X3.1
unnamed: CARD1.P6, CARD1.P7, D12.A
PWR_BAT: CARD0.P8, CARD1.P8; also elsewhere on the board
PWR_CHG: U$2.P3; also elsewhere on the board
USB_DM: U5.6 (IO1_2); also elsewhere on the board
USB_DP: U5.4 (IO2_2); also elsewhere on the board
VIN: D1.A, D4.A, D5.C, D6.C, D11.C, D12.C, D13.C, U6.3 (INPUT)

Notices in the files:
parts and their libraries:
SparkFun-FreqCtrl: Licensing: CC v3.0 Share-Alike You are welcome to use this library for commercial purposes.
